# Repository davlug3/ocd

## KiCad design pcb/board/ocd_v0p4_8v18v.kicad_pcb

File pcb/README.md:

# Phase C — OCD v0.4 PCB (1590B, through-hole)

Electrical source of truth: `circuit/spec/out_ocd_v0p4_8v18v/ocd_v0p4_8v18v.cir`
(copied to `pcb/handoff/ocd_v0p4_8v18v.cir`). The PCB overlay adds board
mechanics, footprints and pin maps; it does not change the schematic.

> **Status: routed, release gates passed (prototype).** The `pcb-design-skill`
> CI pipeline built, routed and checked the board: DRC 0, unconnected 0,
> DFM 0, netlist parity 0 and fab 0 (run 43059805373). See
> `pcb/board/design-report.md`. It is **not** panel-fitted to a specific
> 1590B drilling; that remains the main open mechanical item.

## Board

| Item | Value |
|---|---|
| Size | 108 × 58 mm |
| Layers / thickness / copper | 2 / 1.6 mm / 1 oz |
| Material / finish | FR4 / HASL-LF |
| Assembly | Through-hole (THT) |
| Profile | `2layer-low-speed` |
| Mounting | 4 × M3 non-plated holes, 3.2 mm, at (7,7), (101,7), (7,51), (101,51) mm |

## What is on the board

46 placed parts: 42 electrical + 4 mounting holes.

- **Core circuit:** R1–R15, C1–C11, D1, D_PWR, D_LED, R_LED, M1, M2
  (the SPICE netlist decides connectivity).
- **U1 (DIP-8):** one TL082 package. The SPICE sections `X1A` and `X3A` are
  merged here; they are excluded from the LTspice import.
- **X2 / X4 / X5:** Drive, Tone and Volume pots. They replace the fixed
  simulation placeholders `R_X2POT`, `R_X4`, `R_VOL5A/B`, which are excluded.
- **J_IN / J_OUT:** PCB-mounted 1/4" jacks (Neutrik NMJ6HFD2 stereo in,
  NMJ4HFD2 mono out).
- **J_PWR:** 9 V DC jack, center-negative, switched (CUI/Same Sky PJ-102AH).
- **BT1:** 2-pin header for an off-board 9 V battery snap.
- **SW_FS:** 2×05 header for a panel-mounted 3PDT true-bypass switch.
- **SW_HP:** 1×03 header for the panel-mounted HP/LP toggle.

## Footprint verification

Footprint names and pad numbers were read from the official KiCad library
(S019) and cross-checked against the part datasheets (S007, S008, S016–S018).
They were **not** previewed in the KiCad footprint picker locally because the
Termux environment has no KiCad; the CI build resolves the installed KiCad 9
library and is the compatibility gate. A missing or renamed footprint will
fail the CI build rather than be silently substituted.

## Pin maps that matter

| Part | Footprint | Map | Evidence |
|---|---|---|---|
| M1, M2 (2N7000) | `Package_TO_SOT_THT:TO-92_Inline` | `d=3, g=2, s=1, b=1` | S008 (onsemi NDS7002A): TO-92 1=S, 2=G, 3=D |
| D_PWR, D1, D_LED | KiCad `Diode_THT` / `LED_THT` | anode→pad 2, cathode→pad 1 | S019: KiCad `Device:D`/`LED` pin 1=K, 2=A |
| U1 (TL082) | `Package_DIP:DIP-8_W7.62mm` | 1=X1_OUT, 2=X1_FB, 3=X1_P, 4=GND, 5=CLIP_B, 6=X3_FB, 7=X3_OUT, 8=VCC_F | S007 TL082 DIP-8 pinout |
| X2 (Drive, 1 M) | Alpha RD901F vertical | 1=X1_OUT, 2=X2_W, 3=X2_W | S017 + build check |
| X4 (Tone, 10 k) | Alpha RD901F vertical | 1=TONE_TOP, 2=TONE_W, 3=TONE_W | S002/S017 + build check |
| X5 (Volume, 100 k) | Alpha RD901F vertical | 1=GND, 2=OUT, 3=VOL_TOP | S017 + build check |
| J_IN | Neutrik NMJ6HFD2 | T=J_IN_TIP, S=GND, R=BAT_NEG | S018/S019 |
| J_OUT | Neutrik NMJ4HFD2 | T=J_OUT_TIP, S=GND | S018/S019 |
| J_PWR | PJ-102AH | 1=GND (center), 2=VCC_JACK (sleeve), 3=BAT_POS (switch) | S016 |
| BT1 | 1×02 header | 1=BAT_POS, 2=BAT_NEG | project wiring |
| SW_HP | 1×03 header | 1=SW1_1, 2=VOL_TOP | S002 |

### Pot wiring

The pots are wired as **rheostats**: the unused end is tied to the wiper.

- **Drive:** CW increases the resistance from `X1_OUT` to `X2_W` → more gain.
- **Tone:** CW increases the resistance from `TONE_TOP` to `TONE_W` → brighter.
- **Volume:** CW moves the wiper from `GND` toward `VOL_TOP` → louder.

`S017` confirms pins 1 and 3 are the fixed ends and pin 2 is the wiper, but the
extracted datasheet text does **not** say which end is CW. The board assumes
**pin 1 = CCW, pin 3 = CW**; confirm on the built hardware (C046).

### 3PDT true bypass (SW_FS)

Wire header pin *n* to 3PDT pin *n* 1:1:

| Header | 3PDT pin | Net | Role |
|---|---|---|---|
| 1 | 1 | `J_IN_TIP` | pole 1 throw |
| 2 | 2 | `IN` | pole 1 common → effect input |
| 3 | 3 | `J_OUT_TIP` | pole 1 throw → bypass |
| 4 | 4 | `J_OUT_TIP` | pole 2 throw → effect output |
| 5 | 5 | `OUT` | pole 2 common |
| 6 | 6 | `GND` | pole 2 throw → mute effect output in bypass |
| 7 | 7 | *(open)* | pole 3 throw |
| 8 | 8 | `LED_A` | pole 3 common |
| 9 | 9 | `GND` | pole 3 throw → LED off in bypass |

The LED is **always on** in the electrical model (D_LED from `LED_A` to `GND`).
On the board, 3PDT pole 3 shorts `LED_A` to `GND` in the bypass position, so
the physical LED is on only when the effect is engaged. This is a board-level
deviation from the simulation, not a schematic change. If the switch throws
are reversed, swap header pins 1↔3, 4↔6 or 7↔9 as needed.

### Battery and DC jack

- **DC present:** center pin (pad 1) = `GND`, sleeve (pad 2) = `VCC_JACK`.
  The normally-closed switch (pads 2–3) opens, disconnecting `BAT_POS`.
- **No DC:** pads 2–3 are closed, so `BAT_POS` feeds `VCC_JACK` through the
  same reverse-polarity diode path.
- **Battery negative:** returns through the input jack ring `R` (`BAT_NEG`).
  A mono TS plug shorts the ring to the plug sleeve, completing the battery
  circuit only while a cable is inserted.
- **Polarity:** center-negative, as required by the v0.4 circuit spec.

This relies on the PJ-102AH switch being closed between pads 2–3 with no plug
(S016, distributor description). Bench-check the actual jack before trusting
the battery/DC handover (C045).

## Deviations and open items

1. **Mechanical fit is not closed.** U1, the three pots, the two jacks and the
   four mounting holes are anchored; the DC jack, headers, battery header and
   small parts are auto-placed. The jack noses now sit at the side edges: the
   placement engine was fixed to use each footprint's real bounding-box offset
   (`pcb-design-skill` commit `8f60198`) and to use the text-free mechanical
   bounding box instead of the text-inflated one (`dca3320`, with the F.CrtYd
   courtyard as fallback). The two jacks are at
   different heights (input `y=25`, output `y=33`) to clear the corner mounting
   holes; pot/jack/3PDT heights, panel hole positions and knob clearance still
   need a mechanical drawing and a panel-fit check.
2. **3PDT is panel-mounted.** No verified KiCad 3PDT footprint was found; the
   board exposes a 2×05 header instead.
3. **Pot CW/CCW end assignment** is assumed (C046).
4. **Pot values/tapers** (X2 1 M, X5 100 k) remain unverified from S002 (K7).
5. **D1/M1/M2 are still approximation models** in simulation; the board uses
   real 1N34A/2N7000 packages, but bench behavior must be confirmed (K2).
6. **No performance claim.** Routing/DRC/DFM say the copper is manufacturable
   at the stated rules; they do not certify the audio performance.

## Pipeline notes

- Placement uses a 0.8 mm courtyard-to-courtyard clearance and a 1.27 mm
  search grid. The board is dense enough that 1.0 mm left no room for C9;
  0.8 mm is still well above the 0.2 mm routing clearance.
- Freerouting can emit neckdown tracks below the netclass minimum (observed
  0.1874 mm against 0.2 mm). The route stage clamps SES widths to
  `rules.min_track_width_mm` before import, so the DRC gate sees the board's
  declared minimum.
- The GND zone on B.Cu uses solid pad connections. Thermal relief left SW_FS
  pad 6 starved (one spoke) and pad 9 unconnected; solid connections remove
  that failure mode on a low-power pedal board. Isolated zone islands are
  removed by the fill.
- GND is poured on both layers. A B.Cu-only pour left an isolated island
  around U1/SW_FS that KiCad reported as unconnected; the F.Cu pour stitches
  the layers through the through-hole GND pads. The Specctra export drops the
  pours so Freerouting routes GND as a normal net; the pours are re-added and
  filled after the SES import, and the router's GND vias stitch the layers.
  The Specctra boundary is inset by the edge clearance plus 0.1 mm so the
  router cannot lay copper flush to the board edge.
- A post-placement pass keeps the fixed-part reference text inside the board
  silk margin and pushes overlapping references apart. Placement itself
  ignores text, so edge parts can otherwise clip their reference. Auto-placed
  passives have their silk reference hidden; the reference stays on F.Fab and
  in the position file.
- The connectors, headers, pots, op-amp and mounting holes are marked
  `board_only` because they are not in the SPICE netlist. That is what the
  structural checker's "pad has no net; confirm it is mechanical" warning is
  about.

## Regenerate

```bash
cd /data/data/com.termux/files/home/ocd

# 1) validate the circuit spec (includes the pcb block)
python3 ~/.agents/skills/circuit-design-skill/scripts/design_spec.py \
  validate circuit/spec/ocd_v0p4_8v18v.json

# 2) regenerate the PCB handoff
python3 ~/.agents/skills/circuit-design-skill/scripts/pcb_handoff.py \
  circuit/spec/ocd_v0p4_8v18v.json --out pcb/handoff

# 3) run the PCB pipeline (needs KiCad 9 + Java + Freerouting;
#    the local Termux environment does not have them, so use CI)
python3 ~/.agents/skills/pcb-design-skill/scripts/design_pipeline.py all \
  pcb/handoff/ocd_v0p4_8v18v-pcb.json \
  --ltspice pcb/handoff/ocd_v0p4_8v18v.cir \
  --pin-map pcb/handoff/ocd_v0p4_8v18v-pinmap.json \
  --node-aliases pcb/handoff/ocd_v0p4_8v18v-node-aliases.json \
  --no-ask
```

The CI path used here stages the same files under
`specs/ocd-v0p4/` on the `davlug3/pcb-design-skill` branch `ocd-v0p4` and
dispatches the `Design pipeline` workflow.

## Previews

- `pcb/preview/ocd_v0p4_8v18v_top.png` / `.svg` and `..._bottom.png` / `.svg`:
  quick top/bottom views of the routed board (copper, pads, silkscreen,
  outline). Generated locally from the `.kicad_pcb`; see `pcb/preview/README.md`.
- `pcb/preview/viewer.html`: interactive 3D preview of the full assembly
  (GLB embedded); also `...-3d-top.png` / `-3d-bottom.png` raytraced stills,
  `ocd_v0p4_8v18v.glb` and `ocd_v0p4_8v18v-components.step`.
- `circuit/preview/ocd_v0p4_8v18v.svg` / `.png`: v0.4 schematic preview from
  the generated `.kicad_sch` (symbol grid + global labels, no wires). See
  `circuit/preview/README.md`.
- Gerbers in `pcb/board/fab/gerbers/` open in any Gerber viewer.

## Evidence

- `pcb/board/`: tracked release copy — `ocd_v0p4_8v18v.kicad_pcb`,
  `.kicad_pro`, Gerbers, drill, position file, STEP, IPC-D-356,
  `ocd_v0p4_8v18v-fabrication.zip`, DRC report, route metrics and
  `design-report.md` from CI run 43059805373.
- Gate summary: 46 footprints, 29 nets, 261 track segments, 2 vias, 2 GND
  zones, 1270.7 mm total track length, 0 DRC violations, 0 unconnected,
  0 DFM failures, clean netlist parity.
- `catalog/sources.json`: S016 (PJ-102AH), S017 (Alpha RD901F), S018 (Neutrik
  jacks), S019 (KiCad footprints); S007/S008 for the TL082/2N7000.
- `evidence/claims.jsonl`: C043–C048.
- `pcb/handoff/ocd_v0p4_8v18v-pcb-handoff.md`: generated handoff and warnings.
- `pcb/build/`: transient CI download (gitignored); `pcb/board/` is the
  tracked release copy.

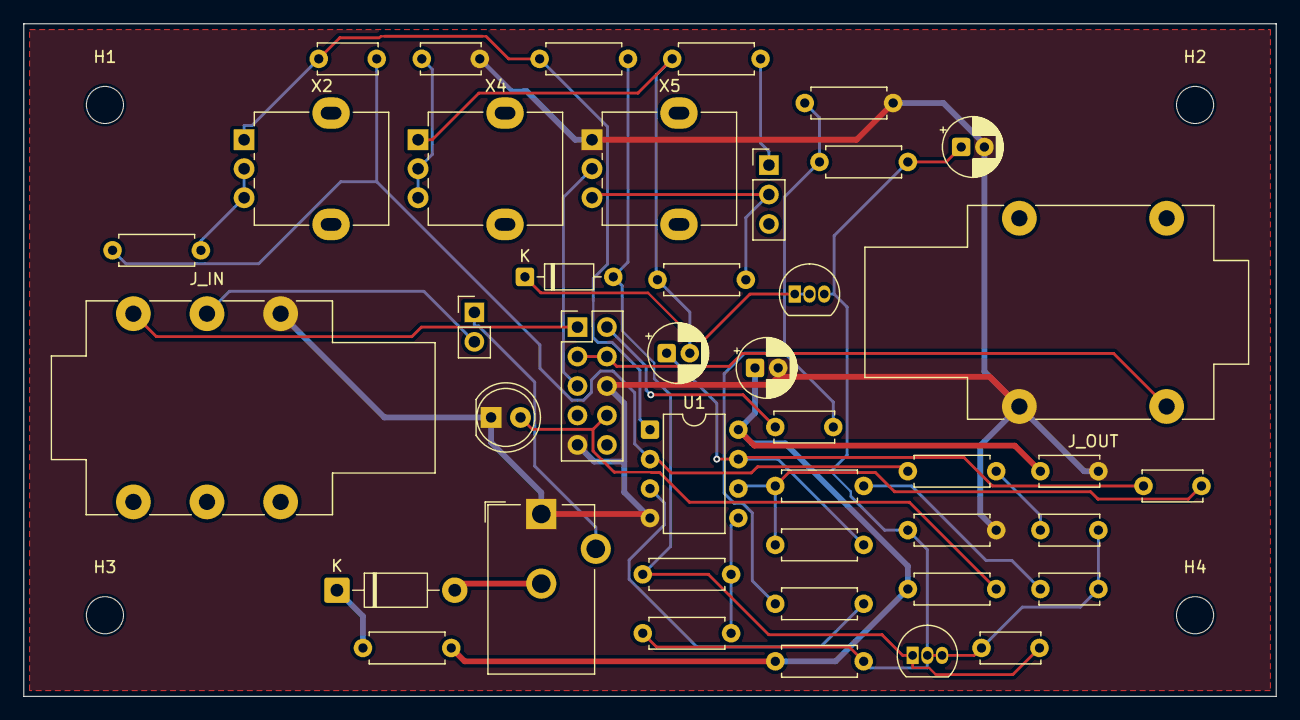
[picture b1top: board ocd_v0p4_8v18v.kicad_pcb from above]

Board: 2 copper layers, 108.0 x 58.0 mm, 46 parts (0 on the bottom side), 28 nets.

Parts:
BT1: BATT; PinHeader_1x02_P2.54mm_Vertical
C1: 22n; C_Disc_D5.0mm_W2.5mm_P5.00mm
C2, C5, C10: 10u; CP_Radial_D5.0mm_P2.00mm
C3, C4, C8: 100n; C_Disc_D5.0mm_W2.5mm_P5.00mm
C6, C9: 220p; C_Disc_D5.0mm_W2.5mm_P5.00mm
C7: 10n; C_Disc_D5.0mm_W2.5mm_P5.00mm
C11: 47n; C_Disc_D5.0mm_W2.5mm_P5.00mm
D1: APPROX_1N34A; D_DO-35_SOD27_P7.62mm_Horizontal
D_LED: LED_RED; LED_D5.0mm
D_PWR: APPROX_1N5819; D_DO-41_SOD81_P10.16mm_Horizontal
H1, H2, H3, H4: M3; MountingHole_3.2mm_M3
J_IN: NMJ6HFD2; Jack_6.35mm_Neutrik_NMJ6HFD2_Horizontal
J_OUT: NMJ4HFD2; Jack_6.35mm_Neutrik_NMJ4HFD2_Horizontal
J_PWR: PJ-102AH; BarrelJack_CUI_PJ-102AH_Horizontal
M1, M2: APPROX_2N7000; TO-92_Inline
R1: 100; R_Axial_DIN0207_L6.3mm_D2.5mm_P7.62mm_Horizontal
R2: 1Meg; R_Axial_DIN0207_L6.3mm_D2.5mm_P7.62mm_Horizontal
R3, R4, R7, R9, R10: 10k; R_Axial_DIN0207_L6.3mm_D2.5mm_P7.62mm_Horizontal
R5: 2.2k; R_Axial_DIN0207_L6.3mm_D2.5mm_P7.62mm_Horizontal
R6: 470k; R_Axial_DIN0207_L6.3mm_D2.5mm_P7.62mm_Horizontal
R8: 18k; R_Axial_DIN0207_L6.3mm_D2.5mm_P7.62mm_Horizontal
R11: 39k; R_Axial_DIN0207_L6.3mm_D2.5mm_P7.62mm_Horizontal
R12: 220k; R_Axial_DIN0207_L6.3mm_D2.5mm_P7.62mm_Horizontal
R13: 150k; R_Axial_DIN0207_L6.3mm_D2.5mm_P7.62mm_Horizontal
R14: 22k; R_Axial_DIN0207_L6.3mm_D2.5mm_P7.62mm_Horizontal
R15: 33k; R_Axial_DIN0207_L6.3mm_D2.5mm_P7.62mm_Horizontal
R_LED: 4.7k; R_Axial_DIN0207_L6.3mm_D2.5mm_P7.62mm_Horizontal
SW_FS: 3PDT; PinHeader_2x05_P2.54mm_Vertical
SW_HP: HP/LP; PinHeader_1x03_P2.54mm_Vertical
U1: TL082; DIP-8_W7.62mm
X2: 1M; Potentiometer_Alpha_RD901F-40-00D_Single_Vertical
X4: 10k; Potentiometer_Alpha_RD901F-40-00D_Single_Vertical
X5: 100k; Potentiometer_Alpha_RD901F-40-00D_Single_Vertical

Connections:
BAT_NEG: BT1.2, J_IN.R
BAT_POS: BT1.1, J_PWR.3
CLIP_A: C7.2, D1.2, M1.1, R9.2, R10.1
CLIP_B: R10.2, R12.2, U1.5
GND: C2.2, C3.2, C5.2, C11.2, D_LED.1, J_IN.S, J_OUT.S, J_PWR.1, R2.2, R7.2, SW_FS.6, SW_FS.9, U1.4, X5.1
IN: C1.1, SW_FS.2
IN_B: C1.2, R2.1, R3.1, R6.1
J_IN_TIP: J_IN.T, SW_FS.1
J_OUT_TIP: J_OUT.T, SW_FS.3, SW_FS.4
LED_A: D_LED.2, R_LED.2, SW_FS.8
M2_D1_NODE: D1.1, M2.1, M2.2
OUT: SW_FS.5, X5.2
SW1_1: R15.2, SW_HP.1
TONE_TOP: C10.2, R14.1, R15.1, X4.1
TONE_W: C11.1, X4.2, X4.3
VCC: D_PWR.1, R1.1
VCC_F: C2.1, C3.1, R1.2, R4.1, R_LED.1, U1.8
VCC_JACK: D_PWR.2, J_PWR.2
VOL_TOP: R14.2, SW_HP.2, X5.3
VREF: C4.2, C5.1, C7.1, C8.2, M1.2, M1.3, M2.3, R4.2, R6.2, R7.1, R12.1
X1_FB: C6.2, R5.1, R8.1, U1.2
X1_OUT: C6.1, R9.1, U1.1, X2.1
X1_P: R3.2, U1.3
X1_RG: C4.1, R5.2
X2_W: R8.2, X2.2, X2.3
X3_FB: C9.2, R11.1, R13.1, U1.6
X3_OUT: C9.1, C10.1, R13.2, U1.7
X3_RG: C8.1, R11.2
